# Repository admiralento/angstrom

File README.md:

# Team Angstrom - Spacecraft Club
Design Files for Femtosat

Push and Pull Schematics and Code here,
I recommend installing GitHub Desktop, it makes the process simplier.

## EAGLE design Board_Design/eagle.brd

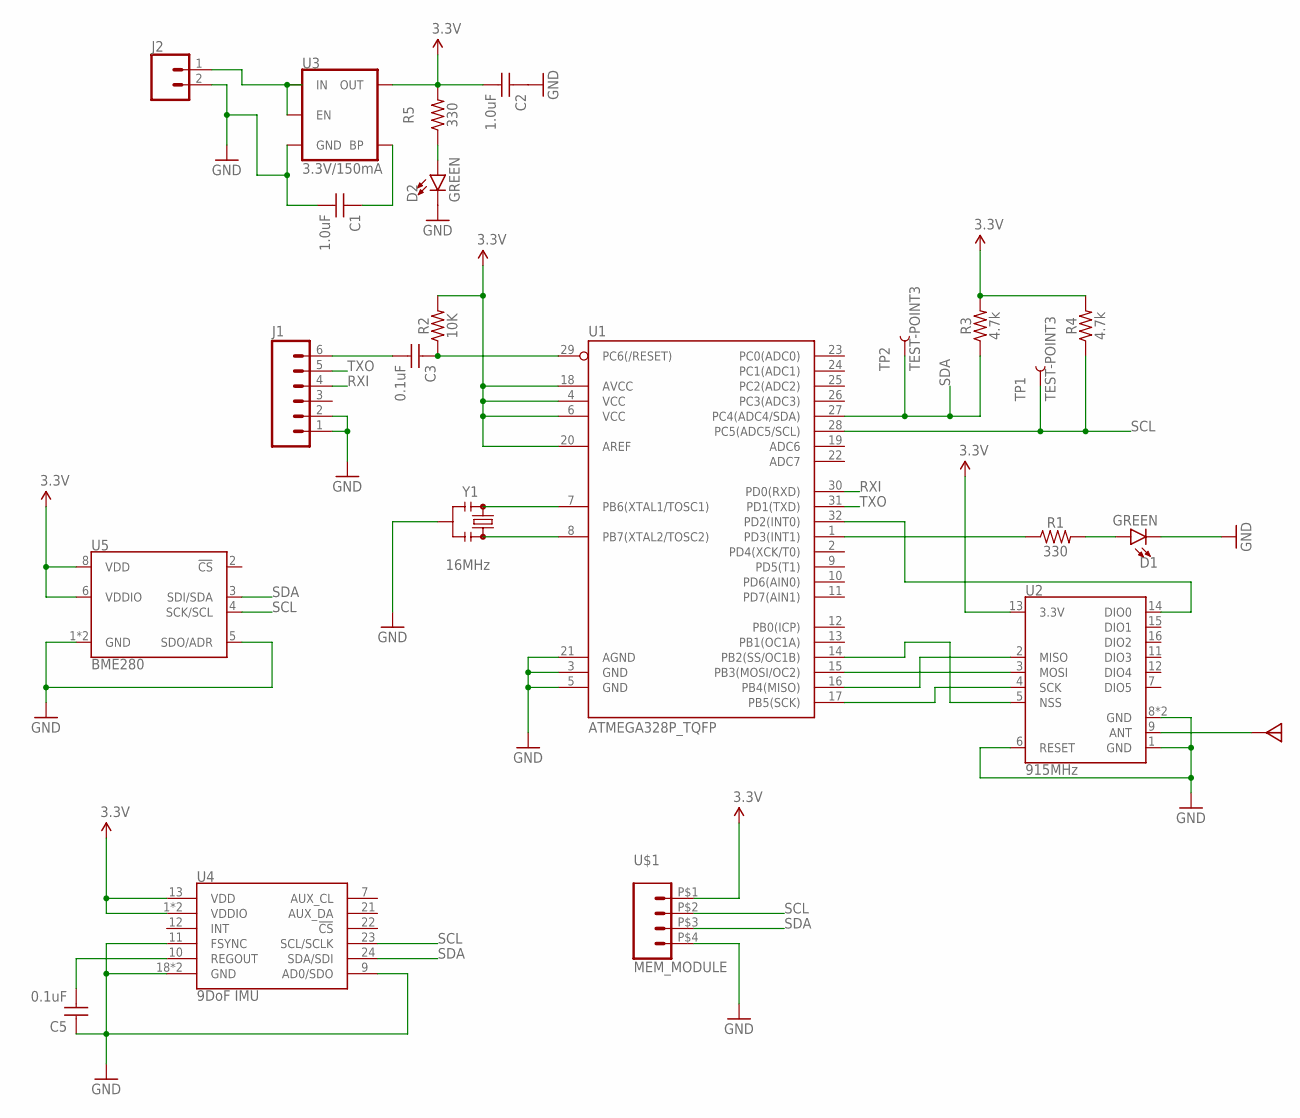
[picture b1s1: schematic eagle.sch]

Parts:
ANT1: ANTENNA_PAD; RFM12B-ANTENNA
C1, C2: 1.0uF; 0603
C3, C5: 0.1uF; 0603-CAP
D1, D2: GREEN; LED-0603
J1: CONNECTOR_6PINSILK_FEMALE_PTH; 1X06
J2: CONNECTOR_2PIN-JST-2MM-SMT; JST-2-SMD
R1, R5: 330; 0603
R2: 10K; 0603-RES
R3, R4: 4.7k; 0603
TP1, TP2: TEST-POINT3; PAD.03X.03
U1: ATMEGA328P_TQFP; TQFP32-08
U2: 915MHz; RFM69HCW-XXXS2
U3: 3.3V/150mA; SOT23-5
U4: 9DoF IMU; QFN24-3X3
U5: BME280; LGA-8-2.5X2.5
U$1: MEM_MODULE; MEM-HEADERS
Y1: 16MHz; RESONATOR-SMD-3.2X1.3

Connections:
3.3V: C2.2, R2.2, R3.2, R4.2, R5.2, U1.4 (VCC), U1.6 (VCC), U1.18 (AVCC), U1.20 (AREF), U2.13 (3.3V), U3.5 (OUT), U4.1 (VDDIO), U4.8 (VDDIO), U4.13 (VDD), U5.6 (VDDIO), U5.8 (VDD), U$1.P$1 (4)
GND: C1.2, C2.1, C5.1, D1.C, D2.C, J1.1, J1.2, J2.2, U1.3 (GND), U1.5 (GND), U1.21 (AGND), U2.1 (GND), U2.6 (RESET), U2.8 (GND), U2.10 (GND), U3.2 (GND), U4.9 (AD0/SDO), U4.11 (FSYNC), U4.18 (GND), U4.20 (GND), U5.1 (GND), U5.5 (SDO/ADR), U5.7 (GND), U$1.P$4 (1), Y1.2
INT: U1.32 (PD2(INT0)), U2.14 (DIO0)
unnamed: U1.16 (PB4(MISO)), U2.2 (MISO)
unnamed: U1.17 (PB5(SCK)), U2.4 (SCK)
unnamed: U1.15 (PB3(MOSI/OC2)), U2.3 (MOSI)
unnamed: J2.1, U3.1 (IN), U3.3 (EN)
unnamed: ANT1.P$1, U2.9 (ANT)
unnamed: U1.14 (PB2(SS/OC1B)), U2.5 (NSS)
unnamed: D2.A, R5.1
unnamed: C1.1, U3.4 (BP)
unnamed: U1.7 (PB6(XTAL1/TOSC1)), Y1.1
unnamed: U1.8 (PB7(XTAL2/TOSC2)), Y1.3
unnamed: D1.A, R1.2
unnamed: R1.1, U1.1 (PD3(INT1))
unnamed: C3.1, R2.1, U1.29 (PC6(/RESET))
unnamed: C3.2, J1.6
unnamed: C5.2, U4.10 (REGOUT)
RXI: J1.4, U1.30 (PD0(RXD))
SCL: R4.1, TP1.P$1, U1.28 (PC5(ADC5/SCL)), U4.23 (SCL/SCLK), U5.4 (SCK/SCL), U$1.P$2 (3)
SDA: R3.1, TP2.P$1, U1.27 (PC4(ADC4/SDA)), U4.24 (SDA/SDI), U5.3 (SDI/SDA), U$1.P$3 (2)
TXO: J1.5, U1.31 (PD1(TXD))

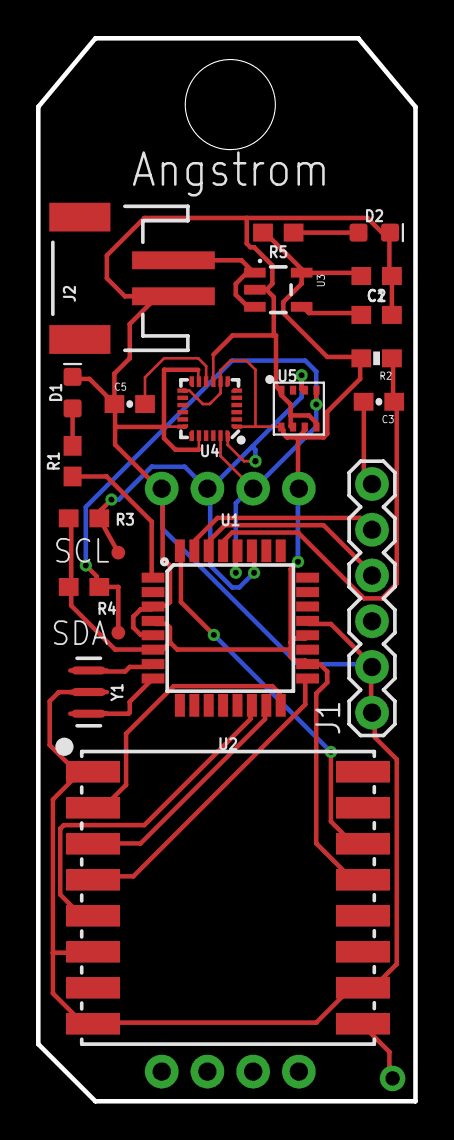
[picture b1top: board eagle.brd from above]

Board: 2 copper layers, 21.0 x 59.1 mm, 23 parts (0 on the bottom side), 22 nets.

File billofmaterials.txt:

Partlist exported from /Users/ammonwolfert/Documents/GitHub/angstrom/Board_Design/eagle.sch at 10/24/19 2:03 PM

Part Value           Device                         Package               Description                                                DIGIKEY              LINK                                         VALUE          
ANT1 ANTENNA_PAD     ANTENNA_PAD                    RFM12B-ANTENNA        Pad for soldering on a wire antenna                                                                                                         
C1   1.0uF           CAPACITOR_1.0UF-0603-16V-10%   0603                  1µF ceramic capacitors                                     399-3118-1-ND                                                     1.0uF          
C2   1.0uF           CAPACITOR_1.0UF-0603-16V-10%   0603                  1µF ceramic capacitors                                     399-3118-1-ND                                                     1.0uF          
C3   0.1uF           CAPACITOR_0.1UF                0603-CAP              CAP-00810                                                  311-1343-1-ND                                                     0.1uF          
C5   0.1uF           CAPACITOR_0.1UF                0603-CAP              CAP-00810                                                  311-1343-1-ND                                                     0.1uF          
D1   GREEN           LED_GREEN0603                  LED-0603              Green SMD LED                                              160-1183-1-ND                                                     GREEN          
D2   GREEN           LED_GREEN0603                  LED-0603              Green SMD LED                                              160-1183-1-ND                                                     GREEN          
J1                   CONNECTOR_6PINSILK_FEMALE_PTH  1X06                  6 pin connection point.                                                                                                                     
J2                   CONNECTOR_2PIN-JST-2MM-SMT     JST-2-SMD             2 pin connector                                            455-1749-1-ND                                                                    
R1   330             RESISTOR_330OHM-0603-1/10W-1%  0603                  330 Ohm resistor                                           311-330GRCT-ND                                                    330            
R2   10K             RESISTOR_10KOHM0603            0603-RES              10k Ohm Resistor                                           311-10KGRCT-ND                                                    10K            
R3   4.7k            RESISTOR_4.7KOHM-0603-1/10W-1% 0603                  4.7k Ohm resistor                                          311-4.7KGRCT-ND                                                   4.7k           
R4   4.7k            RESISTOR_4.7KOHM-0603-1/10W-1% 0603                  4.7k Ohm resistor                                          311-4.7KGRCT-ND                                                   4.7k           
R5   330             RESISTOR_330OHM-0603-1/10W-1%  0603                  330 Ohm resistor                                           311-330GRCT-ND                                                    330            
TP1  TEST-POINT3     TEST-POINT3                    PAD.03X.03            Test Points                                                                                                                                 
TP2  TEST-POINT3     TEST-POINT3                    PAD.03X.03            Test Points                                                                                                                                 
U$1  MEM_MODULE      MEM_MODULE                     MEM-HEADERS                                                                                                                                                       
U1   ATMEGA328P_TQFP ATMEGA328P_TQFP                TQFP32-08             ATMEGA 328P Microcontroller in QFP package                 ATMEGA328P-AURCT-ND                                               ATMEGA328P_TQFP
U2   915MHz          RADIO_RFM69HCW-915             RFM69HCW-XXXS2        Hope RF RFM69H ISM Transceiver Module                                           http://www.anarduino.com/details.jsp?pid=162 915MHz         
U3   3.3V/150mA      VOLTAGE_REGULATOR_MIC52053.3V  SOT23-5               V_REG MIC5205                                              576-1259-1-ND                                                     3.3V/150mA     
U4   9DoF IMU        MPU9250                        QFN24-3X3             MPU-9250 9 Degree of Freedom IMU                           1428-1019-1-ND                                                    9DoF IMU       
U5   BME280          BME280                         LGA-8-2.5X2.5         Bosch BME280 &ndash; Combined Humidity and Pressure Sensor 828-1063-1-ND                                                     BME280         
Y1   16MHz           RESONATOR_16MHZSMD_3.2X1.3     RESONATOR-SMD-3.2X1.3 16MHz Resonator                                            490-1198-1-ND                                                     16MHz

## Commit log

2019-09-22 Added Project Files
    Added Project Files
2019-09-22 Began Schematic and added Radio
2019-09-26 Added Connecter
2019-09-26 Added 2pin connector
2019-09-26 Started Battery Connector
2019-09-26 Added to Battery Connector
2019-09-26 Finished Battery Connector
2019-09-26 Added Clock and LED
2019-09-28 Added 6pin Connecter
    Still dont know where VPROG goes to
2019-09-28 Started Sensor connections
    Started connecting the sensors though I don't know where all the pins should connect.
2019-09-28 Finished Connecting Sensors
    Very unsure if this will work, need to ask lots of questions
2019-10-03 Corrected Capacitors and Resistors
2019-10-03 Added Memory Module
2019-10-03 Passoff Fixes
2019-10-03 Moved Pieces to random location on board
2019-10-04 Routing Almost Complete
2019-10-04 Spanking Cool Femtosat
2019-10-04 Added some words
2019-10-04 Changed Shaped
    May need to shrink its width
2019-10-04 Small Changes
2019-10-04 Small Changes
    Small Changes
2019-10-04 Updated Wire Size
    Still needs to be shrunken to under 22mm in width and wire clearances fixed
2019-10-04 PCB before Trace Ripup
2019-10-04 Redesigned to fit Checklist
2019-10-08 Added Gnd Pour
2019-10-09 Added GND Plane on Back
2019-10-10 Final Checkoff
2019-10-10 Created Arduino code file
2019-10-10 Added backside Silkscreen
2019-10-16 Software Ready for Wednesday
2019-10-17 Fixed library
2019-10-17 Added Wired Pins
2019-10-19 Added Radio
2019-10-19 GROUP WORK
2019-10-19 MPU and BME
2019-10-21 Code for Breakouts
2019-10-21 Organized Code
2019-10-24 Added BME
2019-11-07 Added the Memory Module
2019-11-07 Added Fixed Mem code
2019-11-08 Cleaned up Code
2019-11-12 Adjusted to work with hardware.
2019-11-21 Final Draft Flight Software
2019-11-21 Syntax Fix
2019-12-09 Added Femto Decoder Program
